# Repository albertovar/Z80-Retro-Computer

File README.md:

# Z80 Retro Computer

Zilog Z80A homebrew computer.

## Architecture
- CPU: SGS/ST Z8400AB1 Z80A, 4/8MHz.
- ROM: 28C256, 32 KiB;
- RAM: 24512AK, 64 KiB.
- Standard mode: ROM at 0000h–7FFFh; SRAM at 8000h–FFFFh.
- RAM_ONLY mode: SRAM at 0000h–FFFFh.
  
### Memory map

The Z80 has a 64 KiB address space. The board supports two memory configurations:

#### Standard mode (ROM enabled)

| Z80 address range | Size | Device | Description |
|---|---:|---|---|
| `0000h–7FFFh` | 32 KiB | AT28C256 EEPROM | ROM at the bottom of memory; execution after reset starts here. |
| `8000h–FFFFh` | 32 KiB | SRAM | RAM in the upper half; first RAM address is `8000h`. |

The monitor reserves `F000h–FFFFh` for its buffer, variables and stack. This is a firmware convention, not a hardware reservation.

#### RAM_ONLY mode (ROM disabled)

| Z80 address range | Size | Device | Description |
|---|---:|---|---|
| `0000h–FFFFh` | 64 KiB | SRAM | SRAM occupies the entire address space; ROM is not visible. |

A proposed RAM_ONLY software layout is monitor at `0000h–0FFFh` and user RAM at `1000h–FFFFh`. **This layout and the ROM-to-RAM transition are not implemented or validated yet.**

| Feature | Standard mode | RAMONLY mode |
|---|---|---|
| `0000h–7FFFh` | ROM | SRAM |
| `8000h–FFFFh` | SRAM | SRAM |
| Reset vector `0000h` | ROM | SRAM (must contain valid startup code) |
| RAM available in hardware map | 32 KiB | 64 KiB |

| Port range | Peripheral | Decoder output |
|---|---|---|
| 00h–07h | WD8250 UART | Y0 |
| 08h–0Fh | 82C55 PPI | Y1 |
| 10h–17h | 74HC273 CONTROL latch | Y2 |
| 18h–1Fh | HD44780 LCD | Y3 |
| 20h–27h | LEDs | Y4 |
| 28h–2Fh | Switches / 74HC244 | Y5 |
| 30h–37h | Expansion A | Y6 |
| 38h–3Fh | Expansion B | Y7 |

### Peripherals
- UART: 1.8432 MHz clock, 115200 baud, 8N1, divisor 1.
- PPI: 3 port, 8 bits, I/O general purpose.
- LCD display.
- 8 bit Switches for general purpose.
- 8 bit LEDs for general purpose.

### Boot and monitor

The planned ROM startup performs LCD/banner display, UART initialization, CRC verification and monitor copying. Proposed RAMONLY layout: monitor at 0000h–0FFFh and user RAM at 1000h–FFFFh. **Not implemented or validated yet.** SRAM A15 gating, the copy algorithm and the ROM-disable trampoline require schematic and ASM review.

After initialization, the monitor reports the ROM CRC and RAM test result on the serial console, then displays the command prompt:

The monitor's `help` command lists the available console commands:

### ROM CRC
CRC-16/CCITT-FALSE, initial value FFFFh, polynomial 1021h, MSB-first; covers bytes 0000h–7FFDh; CRC stored at 7FFEh–7FFFh. ROM image is padded to 32768 bytes.

## Programming workflow

The firmware workflow has two paths: creating and programming the boot ROM, and loading test or application binaries into SRAM.

### Build and program the ROM

1. Assemble the monitor ASM source with `z80asm` to produce a raw binary.
2. Run `firmware/utils/make_rom.py` on that binary. It pads the image to 32 KiB, calculates the CRC-16/CCITT-FALSE value and stores it in the final two bytes.
3. Program the generated CRC image (not the raw assembler output) into the AT28C256 using the T48 programmer and Minipro.

Example commands (run from the repository root):

```sh
z80asm -o monitor.bin monitor.asm
python3 firmware/utils/make_rom.py monitor.bin monitor_CRC.bin
minipro -p AT28C256 -w monitor_CRC.bin -s
```

### Serial console

A serial terminal can be opened with `screen` at 115200 baud:

```sh
screen /dev/ttyUSB0 115200
```

Replace `/dev/ttyUSB0` with the serial device assigned to the board if it differs. To exit `screen`, press `Ctrl+A`, then `K`, then confirm with `Y`.

### Load a binary into SRAM over UART

1. Assemble the test or application ASM source into a binary.
2. Connect to the board's UART (115200 baud, 8N1).
3. Run `firmware/utils/sendbin.py` with the serial device, hexadecimal load address and binary filename. The script asks the monitor to receive the file, waits for `READY`, transfers the binary and waits for `loadbin complete`.

Example:

```sh
python3 firmware/utils/sendbin.py /dev/ttyUSB0 8000 SWITCHES_monitor.bin
```

In **standard memory mode**, SRAM starts at `8000h`. The current utility accepts load addresses from `8000h` through `EFFFh` and prevents transfers from entering the monitor's reserved `F000h–FFFFh` area. RAM_ONLY loading is not currently supported by this utility.

Requirements: `z80asm`, Python 3, `pyserial` and `minipro` (with a T48 programmer for EEPROM programming).

See the [monitor firmware README](firmware/monitor/README.md) for the detailed commands, script behavior and implementation notes.

## Validated status
Reset, ROM fetch, execution, HALT, ROM/RAM decoding, LCD, UART, switches and LEDs. Available troubleshooting tools: multimeter, continuity checks, switches and LEDs; no oscilloscope or logic analyzer.

## Documentation
- [Component datasheets and Z80 instruction references](hardware/datasheets.md)
- [Master project context](PROJECT_CONTEXT.md)
- [Memory map](architecture/memory_map.md)
- [Memory decoder](architecture/memory_decoder.md)
- [I/O map](architecture/io_map.md)
- [Boot sequence](architecture/boot_sequence.md)
- [UART](architecture/uart.md)
- [LCD](architecture/lcd.md)
- [Hardware notes](hardware/hardware_notes.md)
- [Prompts](prompts/README.md)
- [Changelog](CHANGELOG.md)

**Status labels:** CONFIRMED = validated; PROPOSED = not implemented; PENDING = requires review or testing. Avoid unnecessary changes to the fabricated PCB.

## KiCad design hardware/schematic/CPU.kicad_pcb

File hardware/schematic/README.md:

# KiCad Schematic
Add .kicad_pro, all hierarchical .kicad_sch sheets, custom symbol library/table and optionally PDF. Inspect actual schematic before advising pin-level changes.

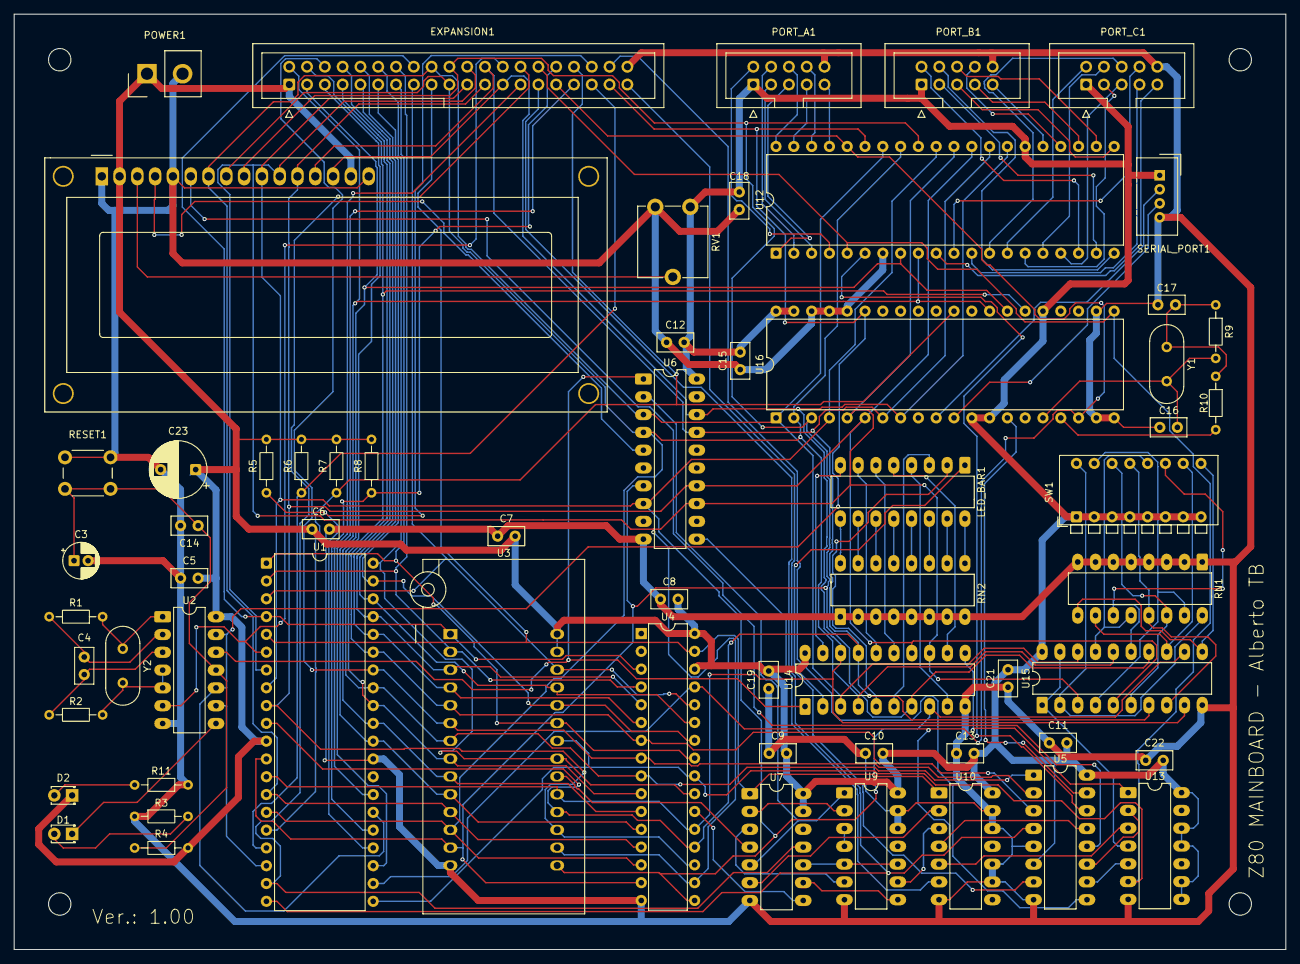
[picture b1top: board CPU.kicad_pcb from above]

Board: 2 copper layers, 181.5 x 133.5 mm, 66 parts (0 on the bottom side), 124 nets.

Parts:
C3: 47uF; CP_Radial_D5.0mm_P2.00mm
C4: 10nF; C_Disc_D5.0mm_W2.5mm_P2.50mm
C5, C6, C7, C8, C9, C10, C11, C12, C13, C14, C15, C18, C19, C21, C22: 100nF; C_Disc_D5.0mm_W2.5mm_P2.50mm
C16: 10pF; C_Disc_D5.0mm_W2.5mm_P2.50mm
C17: 68pF; C_Disc_D5.0mm_W2.5mm_P2.50mm
C23: 470uF; CP_Radial_D8.0mm_P5.00mm
D1: SYSTEM HALT; LED_D1.8mm_W3.3mm_H2.4mm
D2: POWER_ON; LED_D1.8mm_W3.3mm_H2.4mm
DS2: WC1602A
EXPANSION1: IDC-Header_2x20_P2.54mm_Vertical
LED_BAR1: DIP-16_W7.62mm_LongPads
PORT_A1: IDC-Header_2x05_P2.54mm_Vertical
PORT_B1: IDC-Header_2x05_P2.54mm_Vertical
PORT_C1: IDC-Header_2x05_P2.54mm_Vertical
POWER1: Samtec_HPM-02-05-x-S_Straight_1x02_Pitch5.08mm
R1, R2, R3, R10, R11: 1K; R_Axial_DIN0204_L3.6mm_D1.6mm_P7.62mm_Horizontal
R4: 47K; R_Axial_DIN0204_L3.6mm_D1.6mm_P7.62mm_Horizontal
R5, R6, R7, R8: 10K; R_Axial_DIN0204_L3.6mm_D1.6mm_P7.62mm_Horizontal
R9: 1M; R_Axial_DIN0204_L3.6mm_D1.6mm_P7.62mm_Horizontal
REF1, REF2, REF3, REF4: MountingHole_3.2mm_M3
RESET1: SW_PUSH_6mm
RN1: 10K; DIP-16_W7.62mm_LongPads
RN2: 1K; DIP-16_W7.62mm_LongPads
RV1: 47K; Potentiometer_ACP_CA9-V10_Vertical
SERIAL_PORT1: NS-Tech_Grove_1x04_P2mm_Vertical
SW1: SW_DIP_SPSTx08_Piano_CTS_Series194-8MSTN_W7.62mm_P2.54mm
U1: Z80; DIP-40_W15.24mm
U2: 74HC14; DIP-14_W7.62mm_LongPads
U3: ROM 28C256; DIP_Socket-28_W11.9mm_W12.7mm_W15.24mm_W17.78mm_W18.5mm_3M_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
U4: W24512AK; DIP-32_W7.62mm
U5: 74HC138; DIP-16_W7.62mm_LongPads
U6, U14: 74HC273; DIP-20_W7.62mm_LongPads
U7: 74HC04; DIP-14_W7.62mm_LongPads
U9: 74HC08; DIP-14_W7.62mm_LongPads
U10: 74HC32; DIP-14_W7.62mm_LongPads
U12: 82C55A; DIP-40_W15.24mm
U13: 74HC02; DIP-14_W7.62mm_LongPads
U15: 74HC244; DIP-20_W7.62mm_LongPads
U16: 8250; DIP-40_W15.24mm
Y1: 1.8432MHz; Crystal_HC49-4H_Vertical
Y2: 4MHz; Crystal_HC49-4H_Vertical

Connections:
+5V: C5.2, C6.2, C7.2, C8.2, C9.2, C10.2, C11.2, C12.2, C13.2, C15.2, C18.2, C19.2, C21.2, C22.2, C23.1, D2.1 (K), DS2.2 (VDD), DS2.15 (LED(+)), EXPANSION1.1, PORT_A1.1, PORT_B1.1, PORT_C1.1, POWER1.1, R4.1, R5.2, R6.2, R7.2, R8.2, RV1.3, SERIAL_PORT1.1, SW1.1, SW1.2, SW1.3, SW1.4, SW1.5, SW1.6, SW1.7, SW1.8, U1.11 (V_{CC}), U2.14 (VCC), U3.27 (~WE), U3.28 (VCC), U4.30 (CS2), U4.32 (VCC), U5.6 (E2), U5.16 (VCC), U6.20 (VCC), U7.13, U7.14 (VCC), U9.14 (VCC), U10.14 (VCC), U12.26 (VCC), U13.8, U13.9, U13.11, U13.12, U13.14 (VCC), U14.20 (VCC), U15.20 (VCC), U16.12 (CS0), U16.13 (CS1), U16.25 (~ADS), U16.39 (~RI), U16.40 (VCC)
/IO_decoder/CONTROL_PORT_LOAD: U6.11 (Cp), U10.6
/Leds & Switchs/LED_PORT_LOAD: U13.1, U14.11 (Cp)
/Memory_decoder/MEM_ACCESS: U7.10, U9.5, U9.10
/Memory_decoder/RAM_SEL: U9.9, U10.3
/Memory_decoder/ROM_SEL: U9.3, U9.4
A0: EXPANSION1.2, U1.30 (A_{0}), U3.10 (A0), U4.12 (A0), U12.9 (A0), U16.28 (A0)
A1: EXPANSION1.3, U1.31 (A_{1}), U3.9 (A1), U4.11 (A1), U12.8 (A1), U16.27 (A1)
A2: EXPANSION1.4, U1.32 (A_{2}), U3.8 (A2), U4.10 (A2), U16.26 (A2)
A3: EXPANSION1.5, U1.33 (A_{3}), U3.7 (A3), U4.9 (A3), U5.1 (A0)
A4: EXPANSION1.6, U1.34 (A_{4}), U3.6 (A4), U4.8 (A4), U5.2 (A1)
A5: EXPANSION1.7, U1.35 (A_{5}), U3.5 (A5), U4.7 (A5), U5.3 (A2)
A6: EXPANSION1.8, U1.36 (A_{6}), U3.4 (A6), U4.6 (A6)
A7: EXPANSION1.9, U1.37 (A_{7}), U3.3 (A7), U4.5 (A7)
A8: EXPANSION1.10, U1.38 (A_{8}), U3.25 (A8), U4.27 (A8)
A9: EXPANSION1.11, U1.39 (A_{9}), U3.24 (A9), U4.26 (A9)
A10: EXPANSION1.12, U1.40 (A_{10}), U3.21 (A10), U4.23 (A10)
A11: EXPANSION1.13, U1.1 (A_{11}), U3.23 (A11), U4.25 (A11)
A12: EXPANSION1.14, U1.2 (A_{12}), U3.2 (A12), U4.4 (A12)
A13: EXPANSION1.15, U1.3 (A_{13}), U3.26 (A13), U4.28 (A13)
A14: EXPANSION1.16, U1.4 (A_{14}), U3.1 (A14), U4.3 (A14)
A15: EXPANSION1.17, U1.5 (A_{15}), U4.31 (A15), U7.1, U10.1
BUSACK: EXPANSION1.33, U1.23 (~BUSACK)
BUSREQ: EXPANSION1.32, R8.1, U1.25 (~BUSREQ)
CLK_CPU: EXPANSION1.26, U1.6 (CLK), U2.6
CONTROL_CS: U5.13 (~Y2), U10.4
D0: DS2.7 (D0), EXPANSION1.18, U1.14 (D_{0}), U3.11 (D0), U4.13 (D0), U6.3 (D0), U12.34 (D0), U14.3 (D0), U15.18 (1Y0), U16.1 (D0)
D1: DS2.8 (D1), EXPANSION1.19, U1.15 (D_{1}), U3.12 (D1), U4.14 (D1), U6.4 (D1), U12.33 (D1), U14.4 (D1), U15.16 (1Y1), U16.2 (D1)
D2: DS2.9 (D2), EXPANSION1.20, U1.12 (D_{2}), U3.13 (D2), U4.15 (D2), U6.7 (D2), U12.32 (D2), U14.7 (D2), U15.14 (1Y2), U16.3 (D2)
D3: DS2.10 (D3), EXPANSION1.21, U1.8 (D_{3}), U3.15 (D3), U4.17 (D3), U6.8 (D3), U12.31 (D3), U14.8 (D3), U15.12 (1Y3), U16.4 (D3)
D4: DS2.11 (D4), EXPANSION1.22, U1.7 (D_{4}), U3.16 (D4), U4.18 (D4), U6.13 (D4), U12.30 (D4), U14.13 (D4), U15.3 (2Y0), U16.5 (D4)
D5: DS2.12 (D5), EXPANSION1.23, U1.9 (D_{5}), U3.17 (D5), U4.19 (D5), U6.14 (D5), U12.29 (D5), U14.14 (D5), U15.5 (2Y1), U16.6 (D5)
D6: DS2.13 (D6), EXPANSION1.24, U1.10 (D_{6}), U3.18 (D6), U4.20 (D6), U6.17 (D6), U12.28 (D6), U14.17 (D6), U15.7 (2Y2), U16.7 (D6)
D7: DS2.14 (D7), EXPANSION1.25, U1.13 (D_{7}), U3.19 (D7), U4.21 (D7), U6.18 (D7), U12.27 (D7), U14.18 (D7), U15.9 (2Y3), U16.8 (D7)
EXPANSION_PORT_A: EXPANSION1.38, U5.9 (~Y6)
EXPANSION_PORT_B: EXPANSION1.39, U5.7 (~Y7)
GND: C3.2, C5.1, C6.1, C7.1, C8.1, C9.1, C10.1, C11.1, C12.1, C13.1, C14.1, C15.1, C16.2, C17.2, C18.1, C19.1, C21.1, C22.1, C23.2, DS2.1 (VSS), DS2.5 (R/W), DS2.16 (LED(-)), EXPANSION1.40, PORT_A1.10, PORT_B1.10, PORT_C1.10, POWER1.2, R3.1, R11.1, RESET1.1, RN1.1 (R1.1), RN1.2 (R2.1), RN1.3 (R3.1), RN1.4 (R4.1), RN1.5 (R5.1), RN1.6 (R6.1), RN1.7 (R7.1), RN1.8 (R8.1), RN2.1 (R1.1), RN2.2 (R2.1), RN2.3 (R3.1), RN2.4 (R4.1), RN2.5 (R5.1), RN2.6 (R6.1), RN2.7 (R7.1), RN2.8 (R8.1), RV1.1, SERIAL_PORT1.4, U1.29 (GND), U2.7 (GND), U3.14 (GND), U4.16 (VSS), U5.5 (~E1), U5.8 (GND), U6.10 (GND), U7.7 (GND), U9.7 (GND), U9.12, U9.13, U10.7 (GND), U10.9, U10.10, U10.12, U10.13, U12.7 (GND), U13.7 (GND), U14.10 (GND), U15.10 (GND), U16.19 (WR), U16.20 (GND), U16.22 (RD), U16.36 (~CTS), U16.37 (~DSR), U16.38 (~DCD)
HALT: U1.18 (~HALT), U2.9
INT: EXPANSION1.34, R7.1, U1.16 (~INT), U16.30 (INTR)
IORQ: EXPANSION1.29, U1.20 (~IORQ), U5.4 (~E0)
LCD_E: DS2.6 (E), U5.12 (~Y3)
LCD_RS: DS2.4 (RS), U6.5 (Q1)
LEDS_CS: U5.11 (~Y4), U13.2
M1: EXPANSION1.27, U1.27 (~M1)
MREQ: EXPANSION1.28, U1.19 (~MREQ), U7.11
NMI: EXPANSION1.35, R6.1, U1.17 (~NMI)
unnamed: C4.1, R1.2, U2.2
unnamed: C4.2, R2.1, U2.3
unnamed: C3.1, C14.2, R4.2, RESET1.2, U2.11
unnamed: C17.1, R9.1, R10.1, Y1.1
unnamed: D1.2 (A), R3.2
unnamed: D1.1 (K), U2.8
unnamed: D2.2 (A), R11.2
unnamed: DS2.3 (VO), RV1.2
unnamed: R1.1, U2.1, Y2.1
unnamed: R2.2, U2.4, U2.5, Y2.2
unnamed: RN1.16 (R1.2), SW1.16, U15.2 (1A0)
unnamed: RN1.15 (R2.2), SW1.15, U15.4 (1A1)
unnamed: RN1.14 (R3.2), SW1.14, U15.6 (1A2)
unnamed: RN1.13 (R4.2), SW1.13, U15.8 (1A3)
unnamed: RN1.12 (R5.2), SW1.12, U15.17 (2A0)
unnamed: RN1.11 (R6.2), SW1.11, U15.15 (2A1)
unnamed: RN1.10 (R7.2), SW1.10, U15.13 (2A2)
unnamed: RN1.9 (R8.2), SW1.9, U15.11 (2A3)
unnamed: LED_BAR1.9 (K), RN2.16 (R1.2)
unnamed: LED_BAR1.10 (K), RN2.15 (R2.2)
unnamed: LED_BAR1.11 (K), RN2.14 (R3.2)
unnamed: LED_BAR1.12 (K), RN2.13 (R4.2)
unnamed: LED_BAR1.13 (K), RN2.12 (R5.2)
unnamed: LED_BAR1.14 (K), RN2.11 (R6.2)
unnamed: LED_BAR1.15 (K), RN2.10 (R7.2)
unnamed: LED_BAR1.16 (K), RN2.9 (R8.2)
unnamed: U7.2, U9.2
unnamed: U7.3, U9.6
unnamed: U7.9, U9.8
unnamed: U7.6, U10.2
unnamed: LED_BAR1.1 (A), U14.2 (Q0)
unnamed: LED_BAR1.2 (A), U14.5 (Q1)
unnamed: LED_BAR1.3 (A), U14.6 (Q2)
unnamed: LED_BAR1.4 (A), U14.9 (Q3)
unnamed: LED_BAR1.5 (A), U14.12 (Q4)
unnamed: LED_BAR1.6 (A), U14.15 (Q5)
unnamed: LED_BAR1.7 (A), U14.16 (Q6)
unnamed: LED_BAR1.8 (A), U14.19 (Q7)
unnamed: U13.4, U15.1 (1OE), U15.19 (2OE)
unnamed: C16.1, R9.2, U16.16 (XIN), Y1.2
unnamed: R10.2, U16.17 (XOUT)
PA0: PORT_A1.2, U12.4 (PA0)
PA1: PORT_A1.3, U12.3 (PA1)
PA2: PORT_A1.4, U12.2 (PA2)
PA3: PORT_A1.5, U12.1 (PA3)
PA4: PORT_A1.6, U12.40 (PA4)
PA5: PORT_A1.7, U12.39 (PA5)
PA6: PORT_A1.8, U12.38 (PA6)
PA7: PORT_A1.9, U12.37 (PA7)
PB0: PORT_B1.2, U12.18 (PB0)
PB1: PORT_B1.3, U12.19 (PB1)
PB2: PORT_B1.4, U12.20 (PB2)
PB3: PORT_B1.5, U12.21 (PB3)
PB4: PORT_B1.6, U12.22 (PB4)
PB5: PORT_B1.7, U12.23 (PB5)
PB6: PORT_B1.8, U12.24 (PB6)
PB7: PORT_B1.9, U12.25 (PB7)
PC0: PORT_C1.2, U12.14 (PC0)
PC1: PORT_C1.3, U12.15 (PC1)
PC2: PORT_C1.4, U12.16 (PC2)
PC3: PORT_C1.5, U12.17 (PC3)
PC4: PORT_C1.6, U12.13 (PC4)
PC5: PORT_C1.7, U12.12 (PC5)
PC6: PORT_C1.8, U12.11 (PC6)
PC7: PORT_C1.9, U12.10 (PC7)
PPI_CS: U5.14 (~Y1), U12.6 (~CS)
RAM_CS: U4.22 (~CS1), U7.8
RD: EXPANSION1.30, U1.21 (~RD), U3.22 (~OE), U4.24 (~OE), U12.5 (~RD), U13.6, U16.21 (~RD)
RESET: EXPANSION1.37, U1.26 (~RESET), U2.10, U2.13, U12.35 (RESET), U16.35 (MR)
RESET_INV: U2.12, U6.1 (~Mr), U14.1 (~Mr)
ROM_CS: U3.20 (~CS), U7.4
ROM_ENABLE: U6.2 (Q0), U7.5, U9.1
SERIAL-RX: SERIAL_PORT1.2, U16.10 (SIN)
SERIAL-TX: SERIAL_PORT1.3, U16.11 (SOUT)
SWITCH_CS: U5.10 (~Y5), U13.5
UART_CS: U5.15 (~Y0), U16.14 (~CS2)
WAIT: EXPANSION1.36, R5.1, U1.24 (~WAIT)
WR: EXPANSION1.31, U1.22 (~WR), U4.29 (~WE), U10.5, U12.36 (~WR), U13.3, U16.18 (~WR)
